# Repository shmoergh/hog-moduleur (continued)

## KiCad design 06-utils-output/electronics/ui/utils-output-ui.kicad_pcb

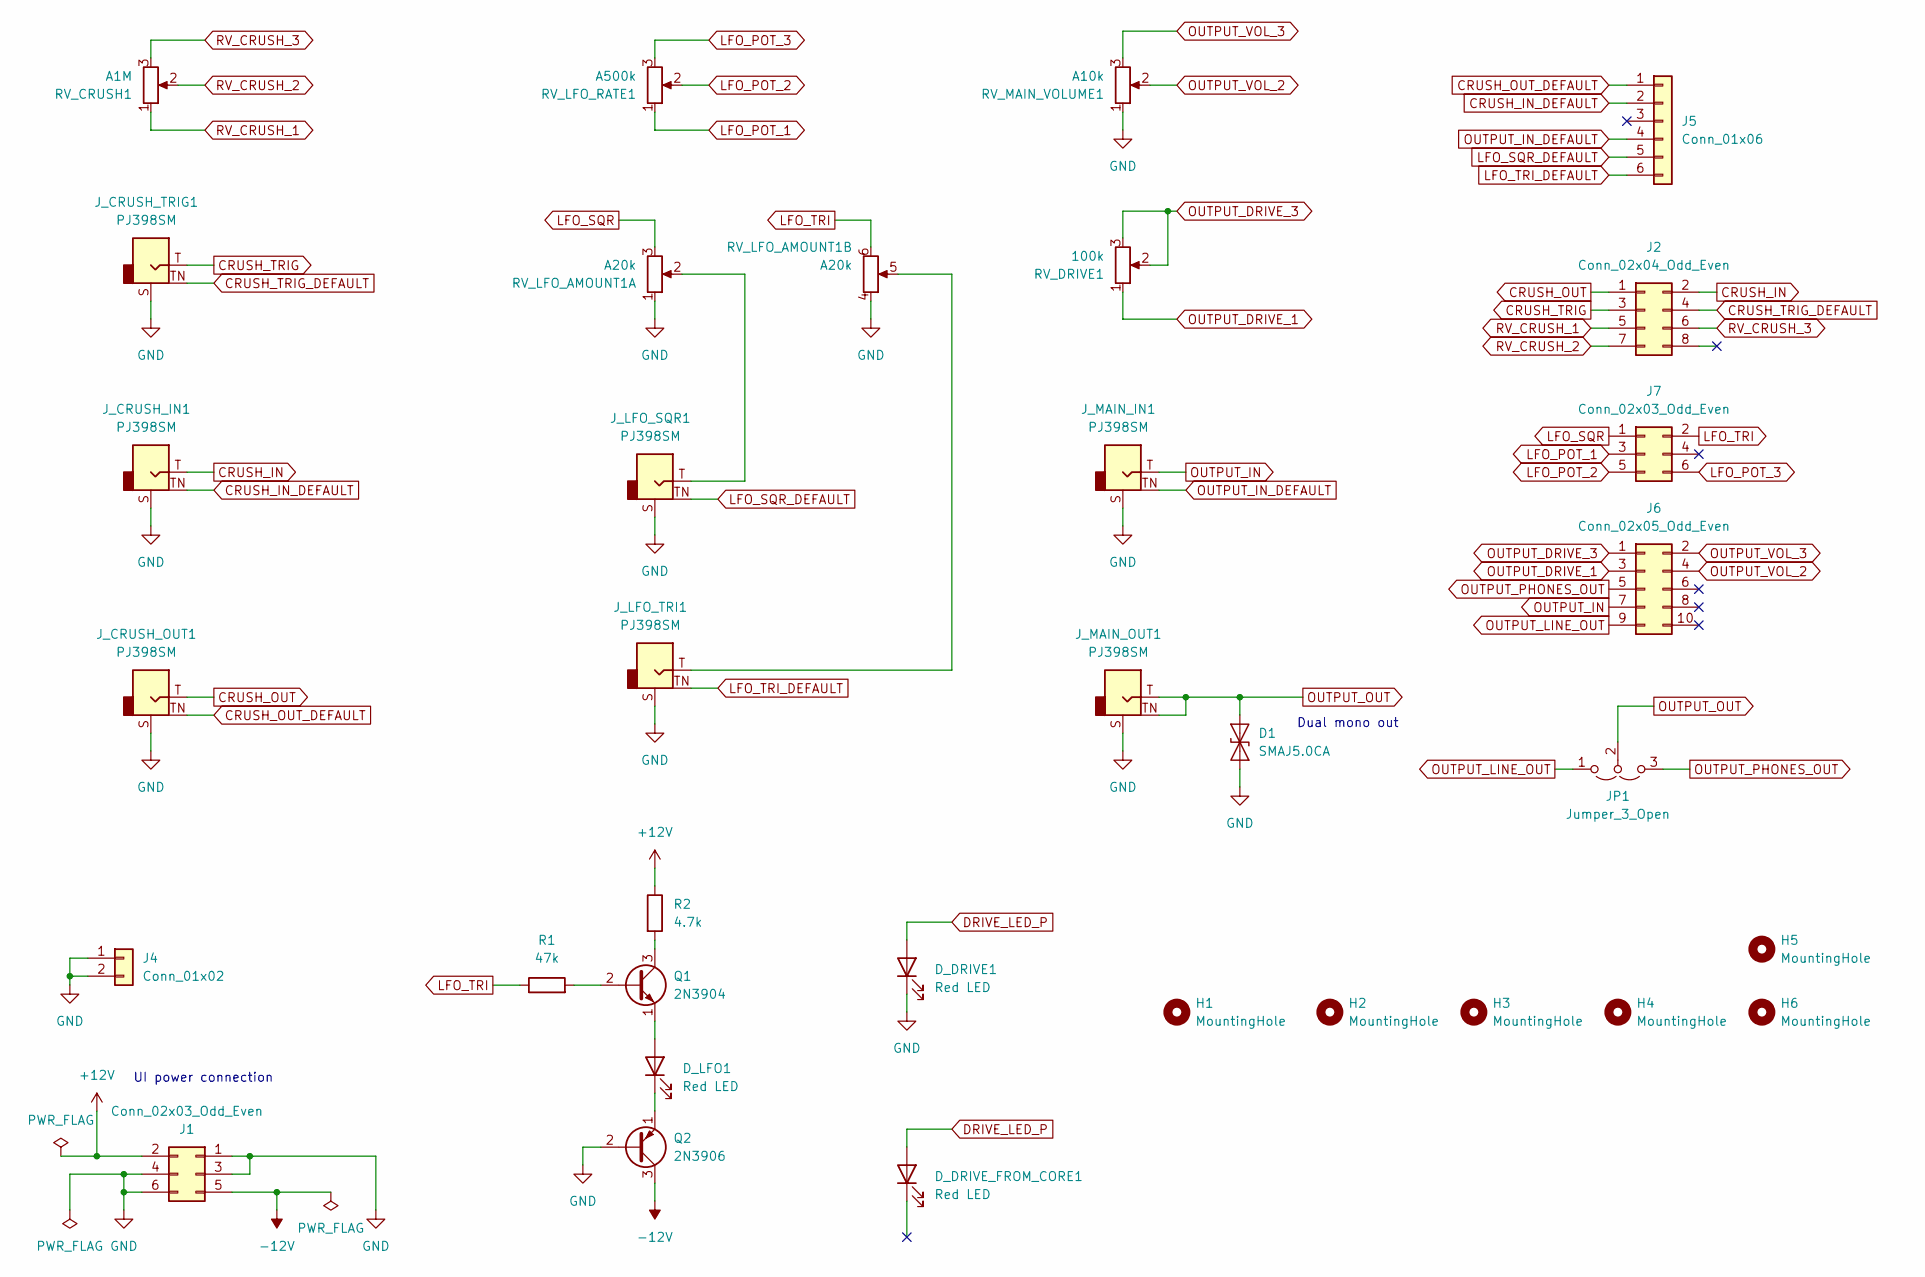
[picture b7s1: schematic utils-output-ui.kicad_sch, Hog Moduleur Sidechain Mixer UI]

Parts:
D1: SMAJ5.0CA; D_SMA
D_DRIVE1: Red LED; LED_D3.0mm
D_DRIVE_FROM_CORE1: Red LED; PinSocket_1x02_P2.54mm_Vertical
D_LFO1: Red LED; LED_D3.0mm
H1, H2, H3, H4, H5, H6: MountingHole; MountingHole_3.2mm_M3_DIN965_Pad
J1: Conn_02x03_Odd_Even; PinSocket_2x03_P2.54mm_Vertical; Part no. 200-SSW10301TD
J2: Conn_02x04_Odd_Even; PinSocket_2x04_P2.54mm_Vertical
J4: Conn_01x02; PinSocket_1x02_P2.54mm_Vertical; Part no. 200-SSW10201TS
J5: Conn_01x06; PinSocket_1x06_P2.54mm_Vertical; Part no. 200-SSW10601TS
J6: Conn_02x05_Odd_Even; PinSocket_2x05_P2.54mm_Vertical
J7: Conn_02x03_Odd_Even; PinSocket_2x03_P2.54mm_Vertical
JP1: Jumper_3_Open; PinHeader_1x03_P2.54mm_Horizontal
J_CRUSH_IN1: PJ398SM; Jack_3.5mm_QingPu_WQP-PJ398SM_Vertical_CircularHoles; Part no. PJ398SM
J_CRUSH_OUT1: PJ398SM; Jack_3.5mm_QingPu_WQP-PJ398SM_Vertical_CircularHoles; Part no. PJ398SM
J_CRUSH_TRIG1: PJ398SM; Jack_3.5mm_QingPu_WQP-PJ398SM_Vertical_CircularHoles; Part no. PJ398SM
J_LFO_SQR1: PJ398SM; Jack_3.5mm_QingPu_WQP-PJ398SM_Vertical_CircularHoles; Part no. PJ398SM
J_LFO_TRI1: PJ398SM; Jack_3.5mm_QingPu_WQP-PJ398SM_Vertical_CircularHoles; Part no. PJ398SM
J_MAIN_IN1: PJ398SM; Jack_3.5mm_QingPu_WQP-PJ398SM_Vertical_CircularHoles; Part no. PJ398SM
J_MAIN_OUT1: PJ398SM; Jack_3.5mm_QingPu_WQP-PJ398SM_Vertical_CircularHoles; Part no. PJ398SM
Q1: 2N3904; TO-92_Inline_Wide
Q2: 2N3906; TO-92_Inline_Wide
R1: 47k; R_Axial_DIN0207_L6.3mm_D2.5mm_P7.62mm_Horizontal
R2: 4.7k; R_Axial_DIN0207_L6.3mm_D2.5mm_P7.62mm_Horizontal
RV_CRUSH1: A1M; Potentiometer_Bourns_Single-PTV09A; Part no. 652-PTV09A4025FB104
RV_DRIVE1: 100k; Potentiometer_Bourns_Single-PTV09A; Part no. 652-PTV09A4025FB104
RV_LFO_AMOUNT1: A20k; Potentiometer_Bourns_Dual-PTV112-4; Part No. 652-PTV1124425AA203
RV_LFO_RATE1: A500k; Potentiometer_Bourns_Single-PTV09A; Part no. 652-PTV09A4025FB104
RV_MAIN_VOLUME1: A10k; Potentiometer_Bourns_Single-PTV09A; Part no. 652-PTV09A4025FB104

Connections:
+12V: J1.2, R2.1
-12V: J1.5, Q2.3 (C)
CRUSH_IN: J2.2, J_CRUSH_IN1.T
CRUSH_IN_DEFAULT: J5.2, J_CRUSH_IN1.TN
CRUSH_OUT: J2.1, J_CRUSH_OUT1.T
CRUSH_OUT_DEFAULT: J5.1, J_CRUSH_OUT1.TN
CRUSH_TRIG: J2.3, J_CRUSH_TRIG1.T
CRUSH_TRIG_DEFAULT: J2.4, J_CRUSH_TRIG1.TN
DRIVE_LED_P: D_DRIVE1.2 (A), D_DRIVE_FROM_CORE1.2 (A)
GND: D1.1 (A1), D_DRIVE1.1 (K), J1.1, J1.3, J1.4, J1.6, J4.1, J4.2, J_CRUSH_IN1.S, J_CRUSH_OUT1.S, J_CRUSH_TRIG1.S, J_LFO_SQR1.S, J_LFO_TRI1.S, J_MAIN_IN1.S, J_MAIN_OUT1.S, Q2.2 (B), RV_LFO_AMOUNT1.1, RV_LFO_AMOUNT1.4, RV_MAIN_VOLUME1.1
LFO_POT_1: J7.3, RV_LFO_RATE1.1
LFO_POT_2: J7.5, RV_LFO_RATE1.2
LFO_POT_3: J7.6, RV_LFO_RATE1.3
LFO_SQR: J7.1, RV_LFO_AMOUNT1.3
LFO_SQR_DEFAULT: J5.5, J_LFO_SQR1.TN
LFO_TRI: J7.2, R1.1, RV_LFO_AMOUNT1.6
LFO_TRI_DEFAULT: J5.6, J_LFO_TRI1.TN
unnamed: D_LFO1.2 (A), Q1.1 (E)
unnamed: D_LFO1.1 (K), Q2.1 (E)
unnamed: J_LFO_SQR1.T, RV_LFO_AMOUNT1.2
unnamed: J_LFO_TRI1.T, RV_LFO_AMOUNT1.5
unnamed: Q1.2 (B), R1.2
unnamed: Q1.3 (C), R2.2
OUTPUT_DRIVE_1: J6.3, RV_DRIVE1.1
OUTPUT_DRIVE_3: J6.1, RV_DRIVE1.2, RV_DRIVE1.3
OUTPUT_IN: J6.7, J_MAIN_IN1.T
OUTPUT_IN_DEFAULT: J5.4, J_MAIN_IN1.TN
OUTPUT_LINE_OUT: J6.9, JP1.1 (A)
OUTPUT_OUT: D1.2 (A2), JP1.2 (C), J_MAIN_OUT1.T, J_MAIN_OUT1.TN
OUTPUT_PHONES_OUT: J6.5, JP1.3 (B)
OUTPUT_VOL_2: J6.4, RV_MAIN_VOLUME1.2
OUTPUT_VOL_3: J6.2, RV_MAIN_VOLUME1.3
RV_CRUSH_1: J2.5, RV_CRUSH1.1
RV_CRUSH_2: J2.7, RV_CRUSH1.2
RV_CRUSH_3: J2.6, RV_CRUSH1.3

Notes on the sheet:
Dual mono out
UI power connection

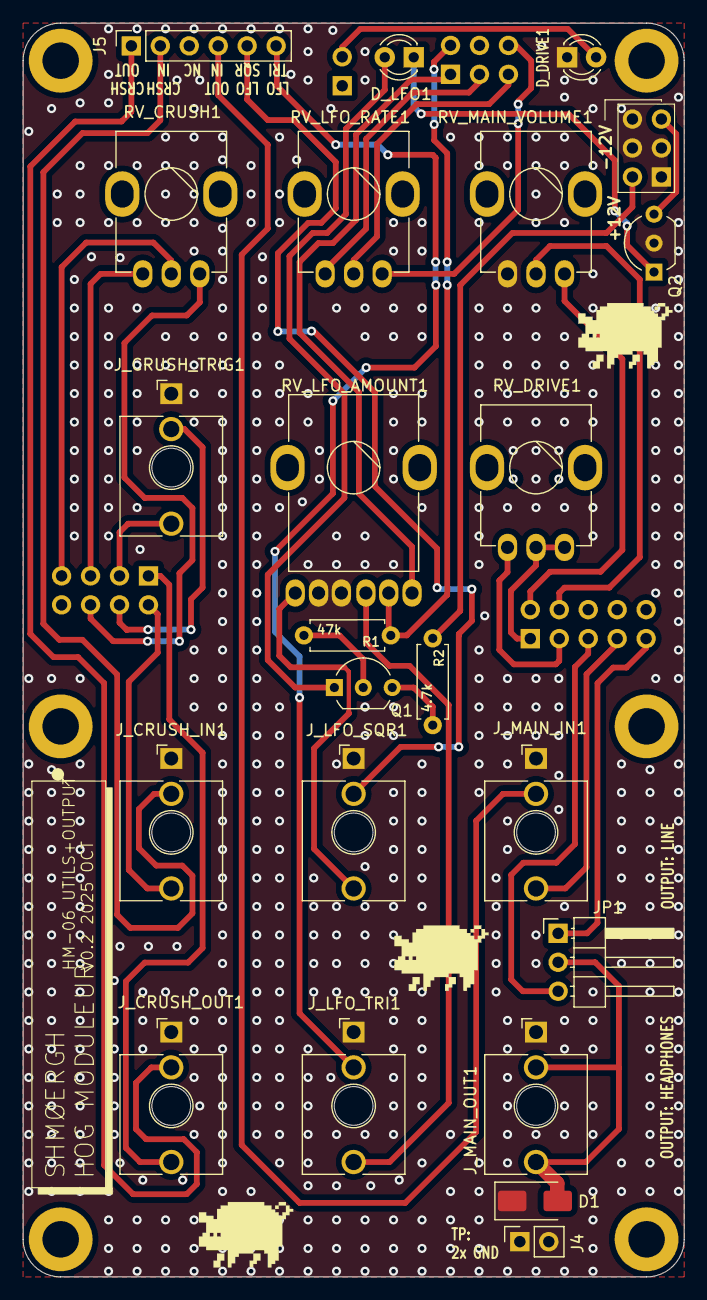
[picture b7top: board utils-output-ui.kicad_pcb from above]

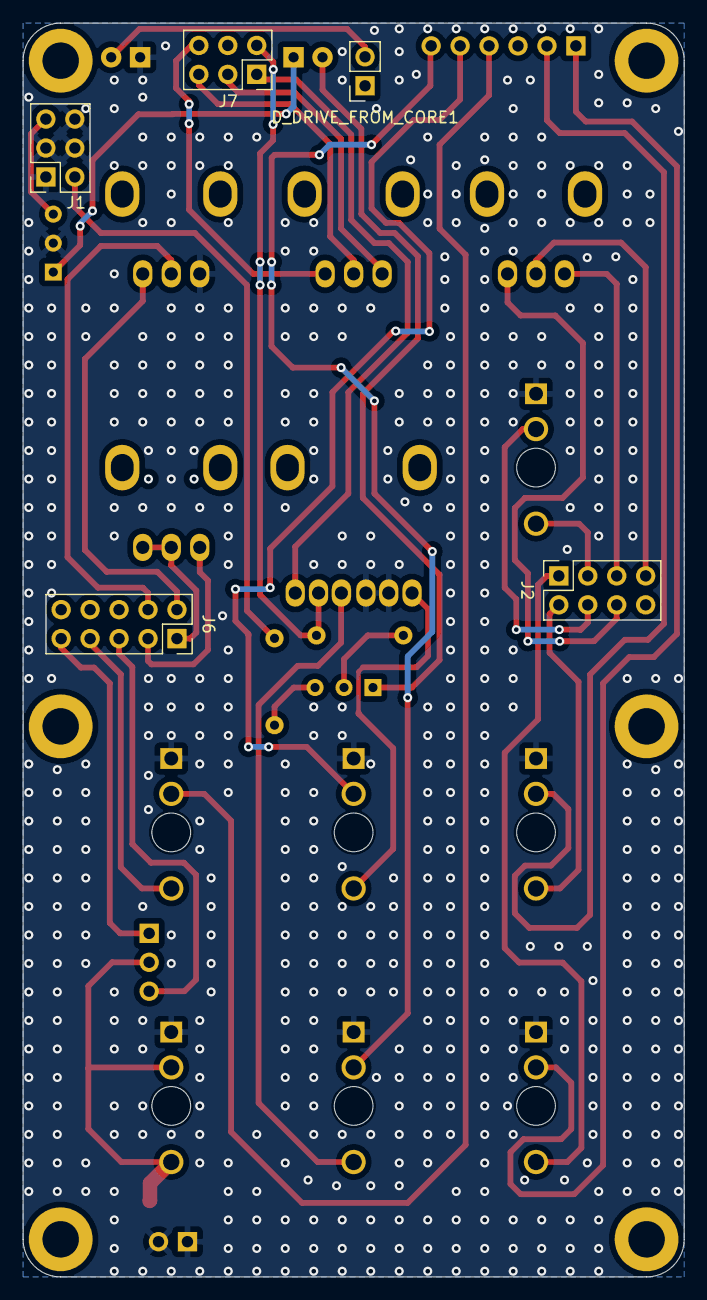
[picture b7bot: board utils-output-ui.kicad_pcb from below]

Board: 2 copper layers, 58.0 x 110.0 mm, 33 parts (5 on the bottom side), 35 nets.

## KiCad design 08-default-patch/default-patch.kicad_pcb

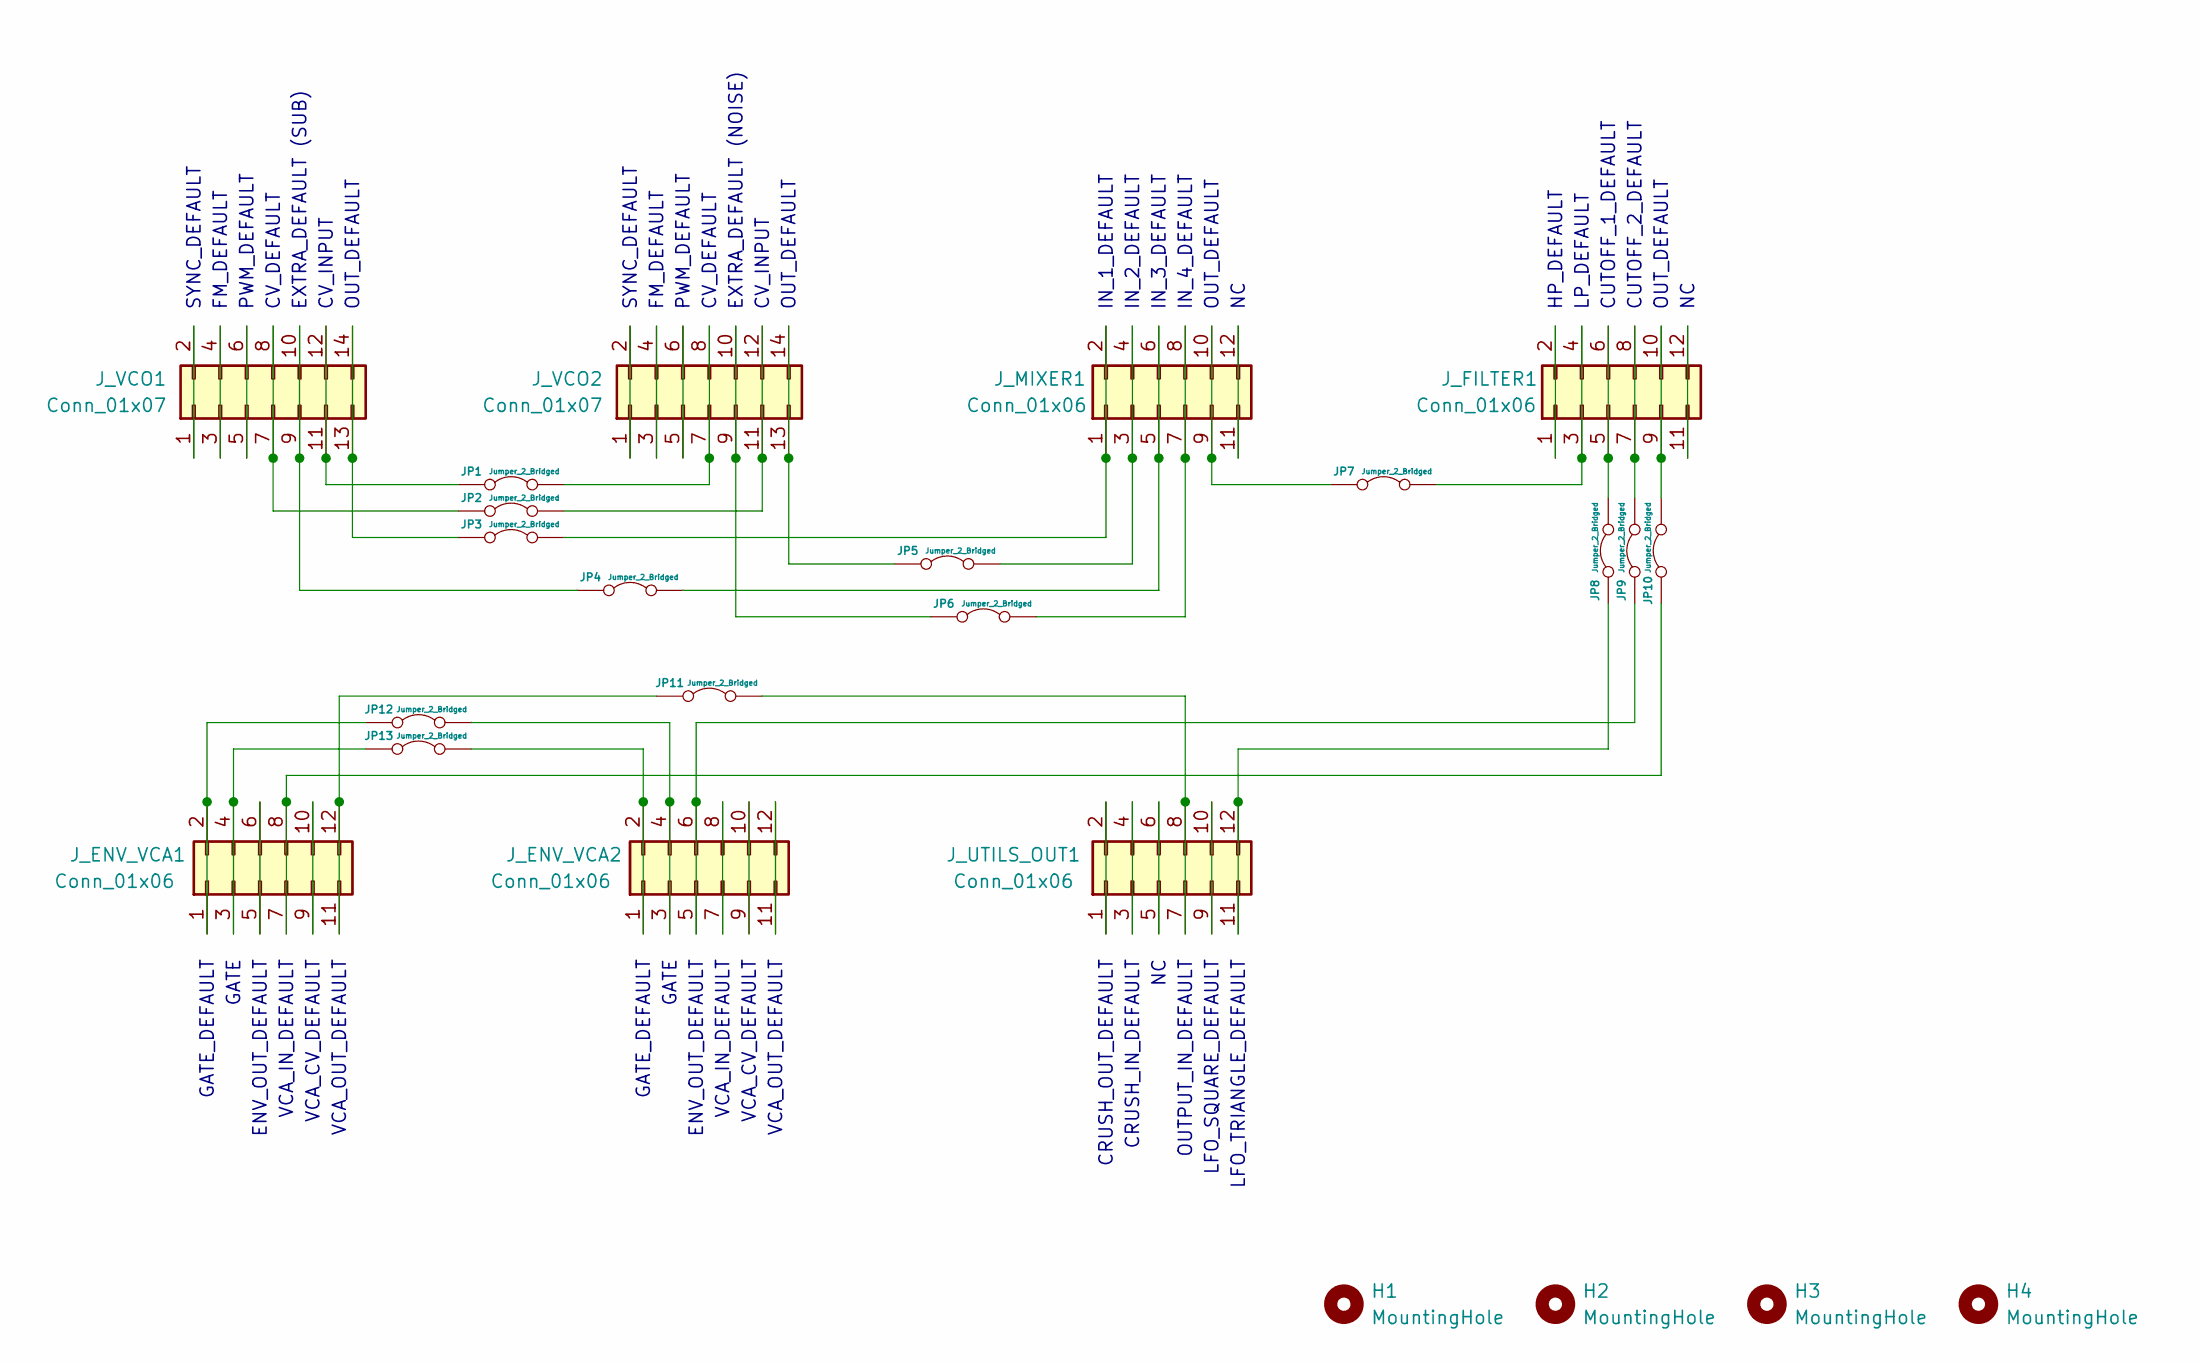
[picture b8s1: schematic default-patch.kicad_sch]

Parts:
H1, H2, H3, H4: MountingHole; MountingHole_3.2mm_M3
JP1, JP2, JP3, JP4, JP5, JP6, JP7, JP8, JP9, JP10, JP11, JP12, JP13: Jumper_2_Bridged; SolderJumper-2_P1.3mm_Bridged_RoundedPad1.0x1.5mm
J_ENV_VCA1, J_ENV_VCA2: Conn_01x06; PinHeader_2x06_P2.54mm_Vertical
J_FILTER1: Conn_01x06; PinHeader_2x06_P2.54mm_Vertical
J_MIXER1: Conn_01x06; PinHeader_2x06_P2.54mm_Vertical
J_UTILS_OUT1: Conn_01x06; PinHeader_2x06_P2.54mm_Vertical
J_VCO1, J_VCO2: Conn_01x07; PinHeader_2x07_P2.54mm_Vertical

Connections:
unnamed: JP1.1 (A), J_VCO1.11, J_VCO1.12
unnamed: JP1.2 (B), J_VCO2.7, J_VCO2.8
unnamed: JP2.1 (A), J_VCO1.7, J_VCO1.8
unnamed: JP2.2 (B), J_VCO2.11, J_VCO2.12
unnamed: JP3.1 (A), J_VCO1.13, J_VCO1.14
unnamed: JP3.2 (B), J_MIXER1.1, J_MIXER1.2
unnamed: JP4.1 (A), J_VCO1.9, J_VCO1.10
unnamed: JP4.2 (B), J_MIXER1.5, J_MIXER1.6
unnamed: JP5.1 (A), J_VCO2.13, J_VCO2.14
unnamed: JP5.2 (B), J_MIXER1.3, J_MIXER1.4
unnamed: JP6.1 (A), J_VCO2.9, J_VCO2.10
unnamed: JP6.2 (B), J_MIXER1.7, J_MIXER1.8
unnamed: JP7.1 (A), J_MIXER1.9, J_MIXER1.10
unnamed: JP7.2 (B), J_FILTER1.3, J_FILTER1.4
unnamed: JP8.1 (A), J_UTILS_OUT1.11, J_UTILS_OUT1.12
unnamed: JP8.2 (B), J_FILTER1.5, J_FILTER1.6
unnamed: JP9.1 (A), J_ENV_VCA2.5, J_ENV_VCA2.6
unnamed: JP9.2 (B), J_FILTER1.7, J_FILTER1.8
unnamed: JP10.1 (A), J_ENV_VCA1.7, J_ENV_VCA1.8
unnamed: JP10.2 (B), J_FILTER1.9, J_FILTER1.10
unnamed: JP11.1 (A), J_ENV_VCA1.11, J_ENV_VCA1.12
unnamed: JP11.2 (B), J_UTILS_OUT1.7, J_UTILS_OUT1.8
unnamed: JP12.1 (A), J_ENV_VCA1.1, J_ENV_VCA1.2
unnamed: JP12.2 (B), J_ENV_VCA2.3, J_ENV_VCA2.4
unnamed: JP13.1 (A), J_ENV_VCA1.3, J_ENV_VCA1.4
unnamed: JP13.2 (B), J_ENV_VCA2.1, J_ENV_VCA2.2
unnamed: J_ENV_VCA1.5, J_ENV_VCA1.6
unnamed: J_ENV_VCA1.9, J_ENV_VCA1.10
unnamed: J_ENV_VCA2.7, J_ENV_VCA2.8
unnamed: J_ENV_VCA2.9, J_ENV_VCA2.10
unnamed: J_ENV_VCA2.11, J_ENV_VCA2.12
unnamed: J_FILTER1.1, J_FILTER1.2
unnamed: J_FILTER1.11, J_FILTER1.12
unnamed: J_MIXER1.11, J_MIXER1.12
unnamed: J_UTILS_OUT1.1, J_UTILS_OUT1.2
unnamed: J_UTILS_OUT1.3, J_UTILS_OUT1.4
unnamed: J_UTILS_OUT1.5, J_UTILS_OUT1.6
unnamed: J_UTILS_OUT1.9, J_UTILS_OUT1.10
unnamed: J_VCO1.1, J_VCO1.2
unnamed: J_VCO1.3, J_VCO1.4
unnamed: J_VCO1.5, J_VCO1.6
unnamed: J_VCO2.1, J_VCO2.2
unnamed: J_VCO2.3, J_VCO2.4
unnamed: J_VCO2.5, J_VCO2.6

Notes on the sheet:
HP_DEFAULT
VCA_IN_DEFAULT
GATE_DEFAULT
SYNC_DEFAULT
OUT_DEFAULT
FM_DEFAULT
PWM_DEFAULT
CV_DEFAULT
ENV_OUT_DEFAULT
VCA_CV_DEFAULT
IN_1_DEFAULT
VCA_OUT_DEFAULT
CRUSH_OUT_DEFAULT
OUTPUT_IN_DEFAULT
GATE
LP_DEFAULT
LFO_TRIANGLE_DEFAULT
IN_4_DEFAULT
CUTOFF_1_DEFAULT
IN_2_DEFAULT
CRUSH_IN_DEFAULT
IN_3_DEFAULT
CUTOFF_2_DEFAULT
EXTRA_DEFAULT (NOISE)
CV_INPUT
EXTRA_DEFAULT (SUB)
LFO_SQUARE_DEFAULT

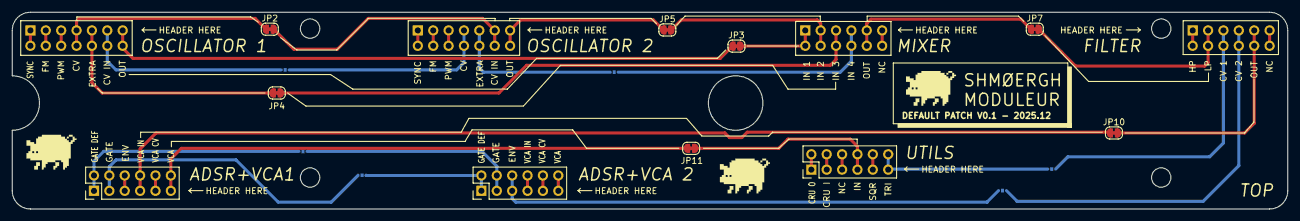
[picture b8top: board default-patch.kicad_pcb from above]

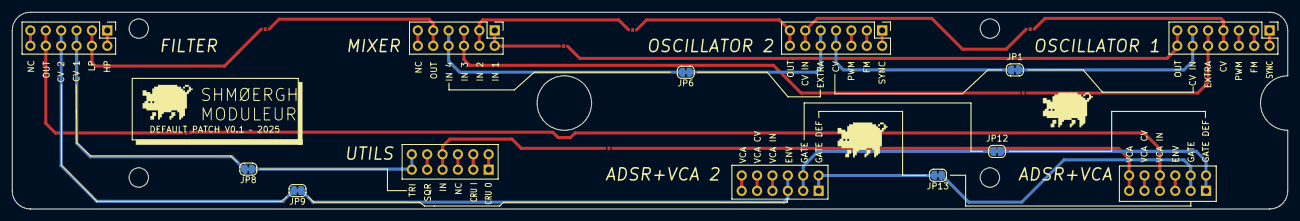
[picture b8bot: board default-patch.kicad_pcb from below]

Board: 2 copper layers, 210.7 x 32.5 mm, 24 parts (10 on the bottom side), 44 nets.

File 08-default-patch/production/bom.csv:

Designator,Footprint,Quantity,Value,LCSC Part #
"JP1, JP10, JP11, JP12, JP13, JP2, JP3, JP4, JP5, JP6, JP7, JP8, JP9",SolderJumper-2_P1.3mm_Bridged_RoundedPad1.0x1.5mm,13,Jumper_2_Bridged,
"J_ENV_VCA1, J_ENV_VCA2, J_FILTER1, J_MIXER1, J_UTILS_OUT1",PinHeader_2x06_P2.54mm_Vertical,5,Conn_01x06,
"J_VCO1, J_VCO2",PinHeader_2x07_P2.54mm_Vertical,2,Conn_01x07,

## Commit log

2025-06-01 Added temporary frame enclosure
    We needed a temporary enclosure, a frame to hold the modules in while we're working on them.
2025-06-01 Added Eurorack Frame readme
2025-06-01 Renamed files
2025-06-09 Added PSU schematics and PCB (v1.0)
2025-06-09 PSU refinements
2025-06-09 Added protection diode and terminal to PSU
2025-06-09 Moved current PSU to Eurorack folder2
2025-06-10 Removed mouse bites
2025-06-15 Added leds to psu
2025-06-15 Added PSU BOM and gerber
2025-06-15 Updated PSU
2025-06-28 Added VCO schematics
2025-07-04 Designed VCO core PCB
2025-07-04 Added whaveshapers to VCO PCB
2025-07-04 Shrink PCB
2025-07-04 Finished VCO Core PCB v0.1
2025-07-04 Added mounting holes to VCO Core PCB
2025-07-04 Added 2-layer version of VCO Core PCB
2025-07-04 Cleanup
2025-07-04 Added test production files
2025-07-04 Deleted 4-layer VCO Core PCB
2025-07-04 Updated tooling holes on VCO Core PCB
2025-07-04 Added labeling
2025-07-05 Added sub & noise circuit to VCO core
2025-07-05 Adjusted screw position and tuning copy on VCO core
2025-07-05 Added AC coupling to noise and sub + 1k outputs
2025-07-05 Added reverse polarity protection VCO core
2025-07-05 Removed lck files
2025-07-05 Added .lck to .gitignore
2025-07-06 Updated noise+sub AC coupling in VCO core
2025-07-06 Refined VCO core back silkscreen
2025-07-06 Repositioned grid origin VCO core PCB
2025-07-06 Added VCO UI board
2025-07-06 Updated sub circuit
2025-07-06 Added VCO UI Plot PDF
2025-07-11 Added default IO conn. to VCO core
2025-07-11 Updated VCO core to use pin headers not sockets
2025-07-12 Added default IO to VCO UI board
2025-07-12 Fixed VCO UI component orientations
    - Wave selector rotary switch had to be rotated
    - Polarity of all pots was reversed
2025-07-12 Plot export
2025-07-13 Refined VCO core and UI
2025-07-13 Added PSU readme
2025-07-14 Added sidechain mixer simulator
2025-07-15 0.1 design of Sidechain Mixer
2025-07-16 Cleanup before PCB order
2025-07-16 Started VCF
2025-07-17 Finished v0.1 of VCF PCB
2025-07-18 Designed UI schematics for VCF
2025-07-19 Designed VCF UI board pre-check
2025-07-19 Added production files to VCF core
2025-07-19 V0.1 VCF PCB checked and ready for prod
2025-07-19 VCF v0.1 proto ordered
2025-07-29 Updated sidechain mixer
2025-07-29 Updated sidechain mixer schematics
2025-07-29 Prepared sidechain mixer PCB
2025-07-31 Fixed VCF v0.1 bugs - new version: v0.2
2025-07-31 Updated VCF UI labels
2025-08-01 SC-Mixer PCB base done
2025-08-01 SC-Mixer PCB updates
2025-08-01 Added SC Mixer UI schematics
2025-08-01 Sidechain Mixer UI PCB RC
2025-08-01 Checked all components on SC-Mixer
2025-08-03 ADSR-VCA first stab
2025-08-03 VCA PCB WIP
2025-08-03 ADSR VCA core PCB done
2025-08-03 Designed ADSR VCA UI PCB
2025-08-06 Updated silkscreen on mixer
2025-08-09 Updated sidechain + ADSR PCB
2025-08-10 Redraw ADSR PCBs to be on top half of the UI
2025-08-10 ADSR+VCA UI PCB done
2025-08-10 Exported ADSR+VCA PCBs
2025-08-10 Removed v0.1 version of ADSR+VCA
2025-08-10 ADSR+VCA production files ready
2025-08-13 Added double defaults pin row to ADSR
2025-08-13 ADSR PCB's production ready
2025-08-13 ADSR production ready - round 2
2025-08-15 Added brain folder
2025-08-15 Started Mod/Output PCB
2025-08-15 Designed LFO & Bitcrush PCB
2025-08-15 1st stab at Mod/Output PCB design
2025-08-16 Started utils & output UI PCB
2025-08-16 Still working on Output UI PCB
2025-08-16 Started swapping output and bitcrusher positions
2025-08-16 Rearranged Utils+Output core PCB
2025-08-16 Redesigned utils + output UI PCB
2025-08-17 Added minimum resistance to LFO CV
2025-08-18 ADSR + VCA v0.2
    - The + and - power pins on the VCA op-amp was accidentally swapped. This version fixes it
2025-08-18 Removed v0.1 ADSR+VCA production files
2025-08-18 Added MIDI input circuit
2025-08-18 Added audio io to Brain
2025-08-18 Added LEDs to Brain
2025-08-19 Redesigned output module
    - The master volume was _before_ the gain control which made no sense because the volume had an effect on how much signal went into the gain stage. Now the master volume is after the diode limiter/cl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
    - Rearranged the output resistors so now line out has a 1k resistor.
    - STILL TODO: the headphone output is not protected against accidental +/-12V inputs.
2025-08-19 Added protection diodes to utils + output
2025-08-20 Bitcrusher tested and refined
2025-08-20 Removed temporary utils + output version
2025-08-21 Fixed Release pot polarity
2025-08-23 Refined utils + output module
2025-08-23 Replaced THT comps. to SMD on ADSR/VCA
2025-08-24 Utils+output PCB v0.1 ready
2025-08-24 Utils+output PCB connectors positions checked
2025-08-24 Utils+output UI PCB done
2025-08-24 Added silkscreen stuff to Utils+output PCB
2025-08-27 Added production files for Utils+output
2025-08-30 Added v0.2 VCO (with octave switch)
2025-08-30 Started octave switch UI design for VCO
2025-08-30 WIP of VCO octave switch UI
2025-08-31 Designed v0.2 VCO UI (with octave switch)
2025-08-31 Added v0.2 PSU
2025-09-03 Brain schematics WIP
2025-09-04 Added boilerplate for Brain code
2025-09-04 Added empty brain-ui library
2025-09-04 Added coding conventions
2025-09-04 Added shell script to create new Brain programs
2025-09-04 Updated conventions
2025-09-05 Added pico-sdk as a submodule
2025-09-05 Added basic docs
2025-09-05 Added Clang Format and instructions to Brain
2025-09-05 Updated new program script format
2025-09-05 Added a task to debug launch to trigger a build
2025-09-05 Messing with C code formatter
2025-09-05 Moved button to brain-ui
2025-09-05 Added basic button component:
2025-09-05 Updated todo name
2025-09-05 Added pot component
2025-09-05 Added hardware test program
2025-09-05 Removed blinky
2025-09-05 Renamed cc files to cpp
2025-09-06 Updated formatting
2025-09-06 Updated AI instructions
2025-09-06 Updated Brain readme
2025-09-06 Added LED component to Brain (untested)
2025-09-07 Updated Brain schematics
2025-09-07 LED sort of works
2025-09-07 Updated LED component blink logic
2025-09-07 Added pot mux logic
2025-09-07 Added pulse component to Brain (untested)
2025-09-07 Reformatted the button component in Brain
2025-09-07 Reformatted the LED component
2025-09-07 Added docs to pot multiplexer
2025-09-07 Removed example project
2025-09-07 Added docs to button and led in Brain
2025-09-07 Deleted unused pot component
2025-09-07 Cleaned up tests
2025-09-07 Updated Button test
2025-09-07 Added pulse component and tests to Brain
2025-09-07 Added note to Brain schematics
2025-09-08 Removed ai folder
2025-09-08 Updated gitignore
2025-09-08 Added MIDI parser class
2025-09-08 Added UART processing in MIDI class
2025-09-08 Updated settings in Brain
2025-09-08 Updated docs
2025-09-08 Updated pulse to use Brain global GPIO settings
2025-09-08 Added common lib to Brain
2025-09-08 Fixed types bug in Brain
2025-09-08 Updated Potmux to use default config
2025-09-08 Updated MIDI in Brain to use defaultS
2025-09-08 Added LED and BUTTON id's in Brain SDK
2025-09-09 PSU v0.2 and fixed crosstalk on VCA
    - added PSU v0.2
    - VCA had a crosstalk issue. The input signal got superimposed on the output. The current solution is to move the input voltage divider on the core board as close to the input pin header connection a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
2025-09-09 Added a note to the VCA board about crosstalk
2025-09-10 Redesigned VCF PCB to avoid crosstalk
    - There's been quite a bit of crosstalk between the input and output of the VCF module. This PCB design attemtps to separate the input and output so that the crosstalk is minimized.
2025-09-10 Tested Brain MIDI module
2025-09-10 Add AGENTS.md with Brain SDK repo guidelines
    Document project structure (lib/programs/pico-sdk/build/docs) and module scopes
    Provide build/flash commands and new-program scaffolding steps
    Capture coding style (clang-format), file layout, and naming
    Outline testing approach using hardware-test apps
    Note commit/PR conventions and security/config tips
2025-09-10 Added AudioCVOut class to BrainSDK (untested)
2025-09-10 Filename cleanup in BrainSDK
2025-09-10 Updated CMake in BrainSDK to use lib folder in includes
2025-09-10 Added Audio CV in to BrainSDK (untested)
2025-09-11 Fixed DAC SPI bug in BrainSDK
2025-09-12 Genius level shifter in Brain output
2025-09-12 Audio/CV out BrainSDK tested/working
2025-09-12 Tested Audio/CV input in BrainSDK (works)
2025-09-12 Design Brain/Core PCB
2025-09-13 Brain PCB WIP
2025-09-13 Designed Brain UI PCB
2025-09-13 Added decoupling caps to DAC in Brain
2025-09-13 Refined Brain PCBs
2025-09-14 Added Adafruit USB-C breakout
2025-09-14 Started via stitching on Brain Core
2025-09-16 More stitching on Brain
2025-09-19 Brain core PCB design WIP
2025-09-21 Updated USB-C breakout on Brain Core
2025-09-21 Brain electronics prod ready
2025-09-21 Brain v0.1 boards ready for prod
2025-09-22 Updated LFO LED resistor value
2025-10-19 Updated brain
2025-10-19 Working on MIDI2CV
2025-10-19 MIDI2CV - keep voltage after gate off
2025-10-19 Added calibration
2025-10-19 Fine tuned MIDI2CV
2025-10-20 Brain update
2025-10-24 Added v0.2 LFO schemati and core PCB
2025-10-24 Updated LFO LED to work from +/-12V
2025-10-24 Added via stitching to LFO UI board
2025-10-24 Updated LFO default patch connector
2025-10-24 Utils/Output v0.2 (deleted v0.1)
2025-10-24 Added VCO output to default connector
2025-10-24 Updated VCO version number on PCB
2025-10-25 Added CV output to VCO default patch
2025-10-25 Swapped DC/DC converter from back to front on PSU PCB
2025-10-25 Added via stitching to VCF
2025-10-25 Moved LED from ADSR core to UI board
2025-10-25 Updated Brain button footprint
2025-10-25 Added TP pads for Brain core
2025-10-25 Removed one pot and added one button in Brain
2025-11-03 Added combined PJ301 and PJ342 jack footprint
2025-11-08 Updated LEDs in MIDI2CV
2025-11-22 Added Default patch PCB
2025-11-22 Updted min LFO resistor footprint for THT
2025-11-22 Updated pull-up for MIDI opto in v0.2 Brain
2025-11-22 Added output buffer to Brain
2025-11-22 Added CV gain trimmer to Brain
